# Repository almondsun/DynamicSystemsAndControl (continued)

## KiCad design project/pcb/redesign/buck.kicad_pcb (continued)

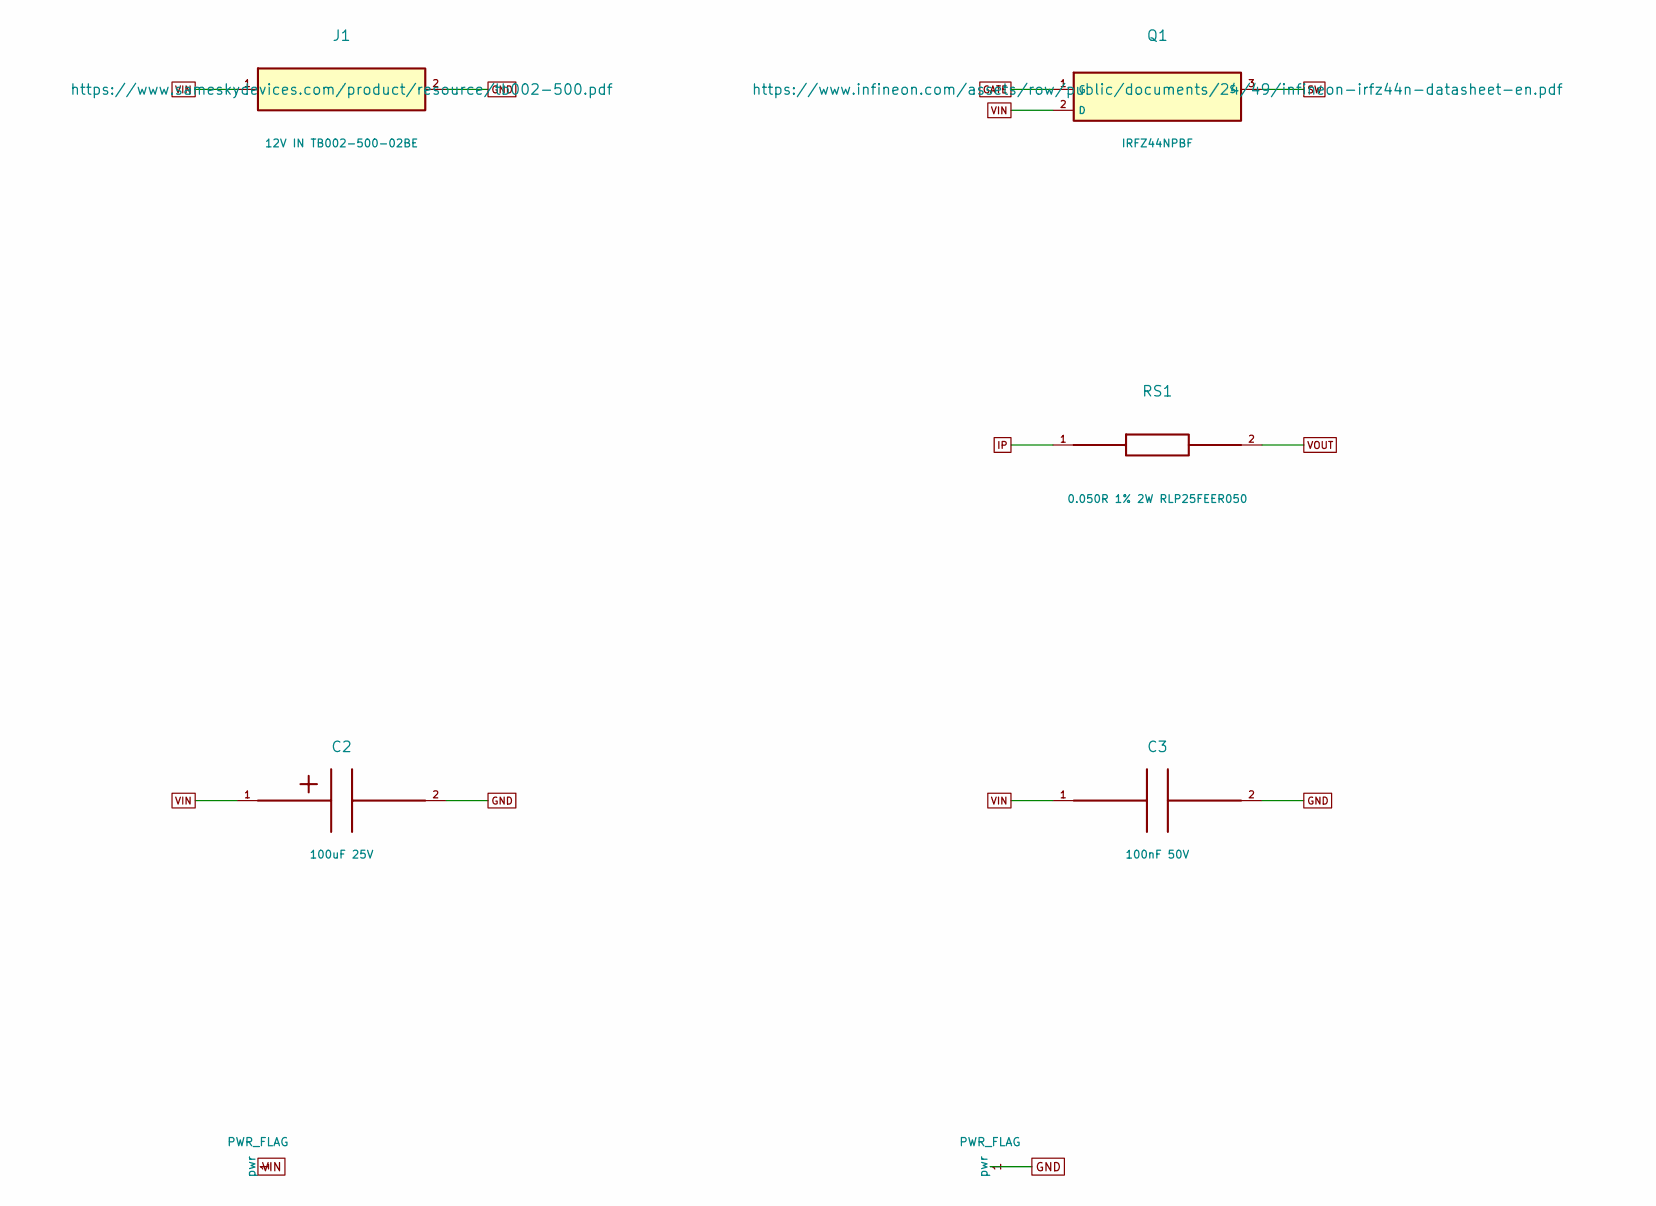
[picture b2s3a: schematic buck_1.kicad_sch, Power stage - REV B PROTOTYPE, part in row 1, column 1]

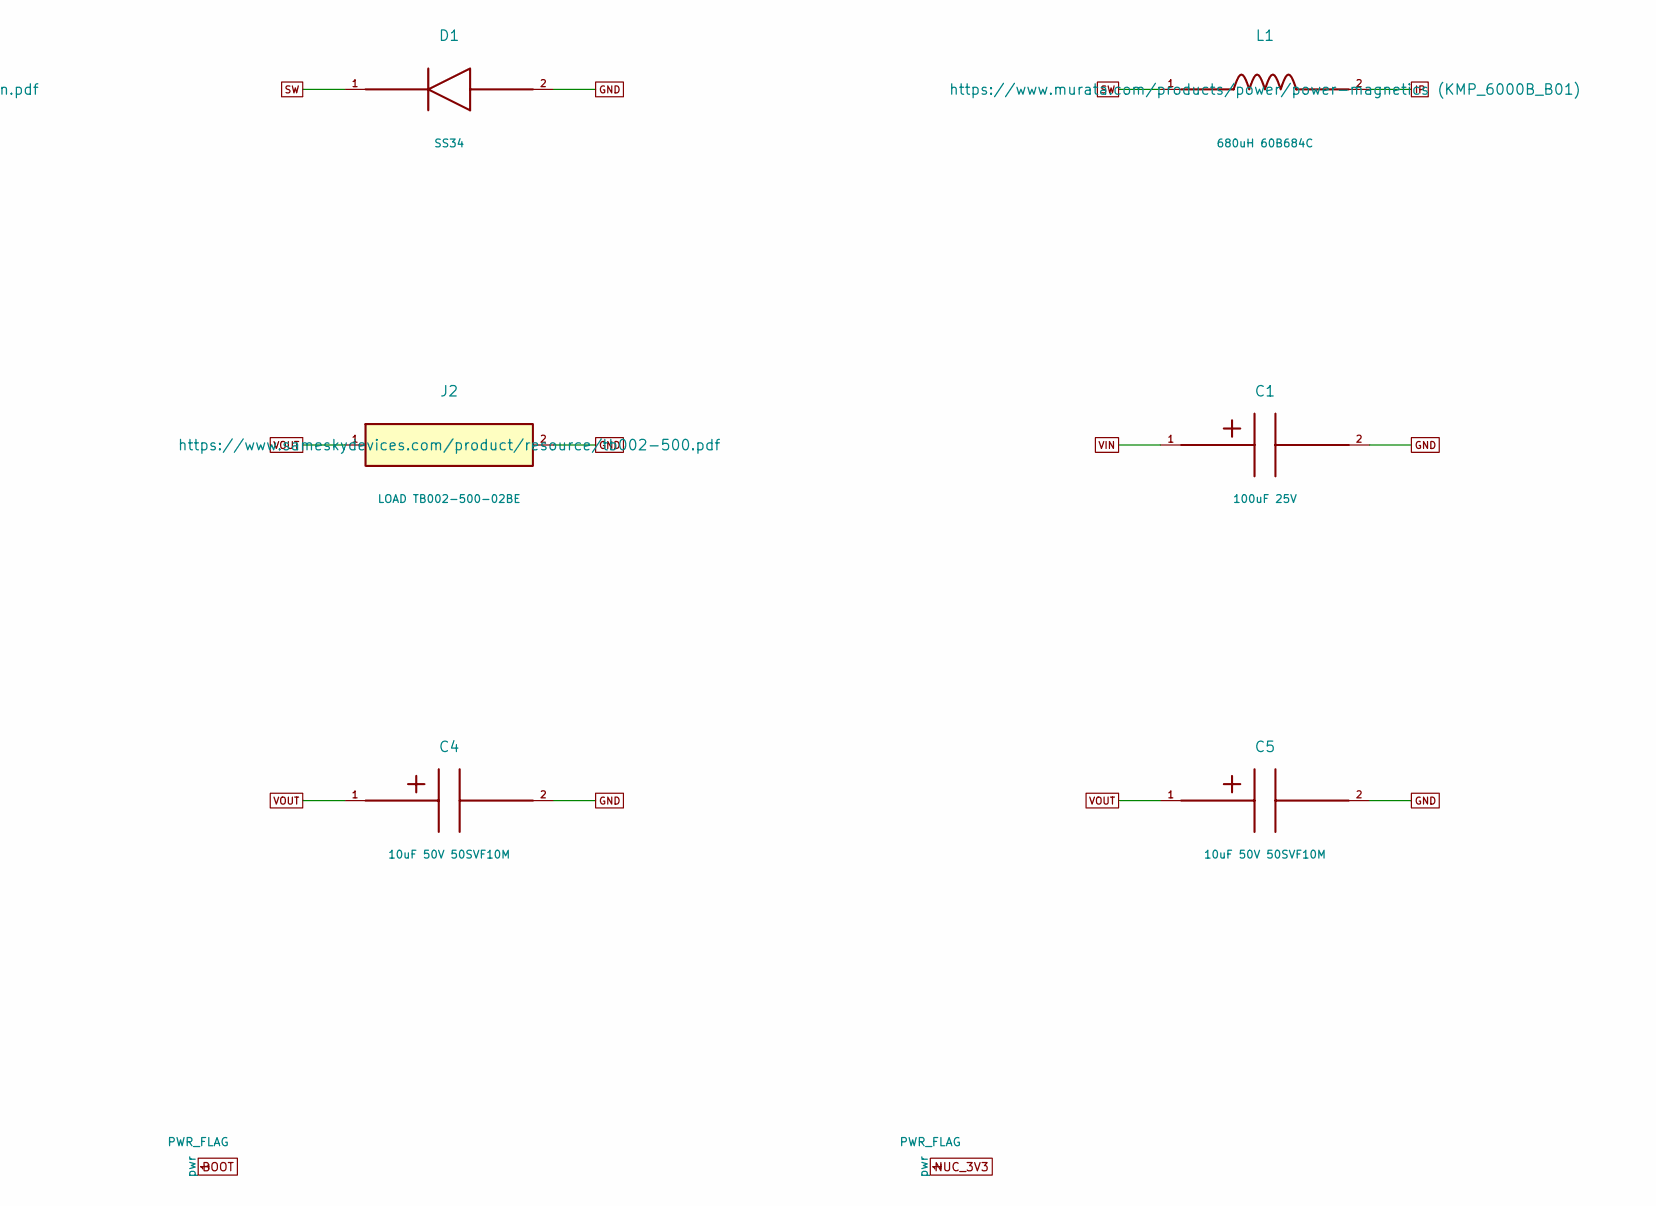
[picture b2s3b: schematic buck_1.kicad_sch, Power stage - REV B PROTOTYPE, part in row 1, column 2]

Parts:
C1, C2: 100uF 25V; CP_Panasonic_SVPF_E7_Land; MPN Panasonic 25SVPF100M; LCSC C136279
C3: 100nF 50V; C_0603_1608Metric; MPN Yageo CC0603KRX7R9BB104; LCSC C14663
C4, C5: 10uF 50V 50SVF10M; CP_Panasonic_SVF_C6_Land; MPN Panasonic 50SVF10M; LCSC C454354
D1: SS34; D_SMA; MPN SS34; LCSC C8678
J1: 12V IN TB002-500-02BE; TerminalBlock_SameSky_TB002-500-02_1x02_P5.00mm; MPN TB002-500-02BE; LCSC C2757858
J2: LOAD TB002-500-02BE; TerminalBlock_SameSky_TB002-500-02_1x02_P5.00mm; MPN TB002-500-02BE; LCSC C2757858
L1: 680uH 60B684C; L_Murata_6000B_27.0x23.5mm; MPN 60B684C; LCSC C6095796
Q1: IRFZ44NPBF; TO-220-3_Vertical_Drill1.4; MPN IRFZ44NPBF; LCSC C2586
RS1: 0.050R 1% 2W RLP25FEER050; R_TAI_RLP25_2512_Kelvin; MPN TA-I RLP25FEER050; LCSC C160588

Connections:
GATE: Q1.1 (G); also elsewhere on the board
GND: C1.2, C2.2, C3.2, C4.2, C5.2, D1.2, J1.2, J2.2; also elsewhere on the board
IP: L1.2, RS1.1; also elsewhere on the board
SW: D1.1, L1.1, Q1.3 (S); also elsewhere on the board
VIN: C1.1, C2.1, C3.1, J1.1, Q1.2 (D); also elsewhere on the board
VOUT: C4.1, C5.1, J2.1, RS1.2; also elsewhere on the board

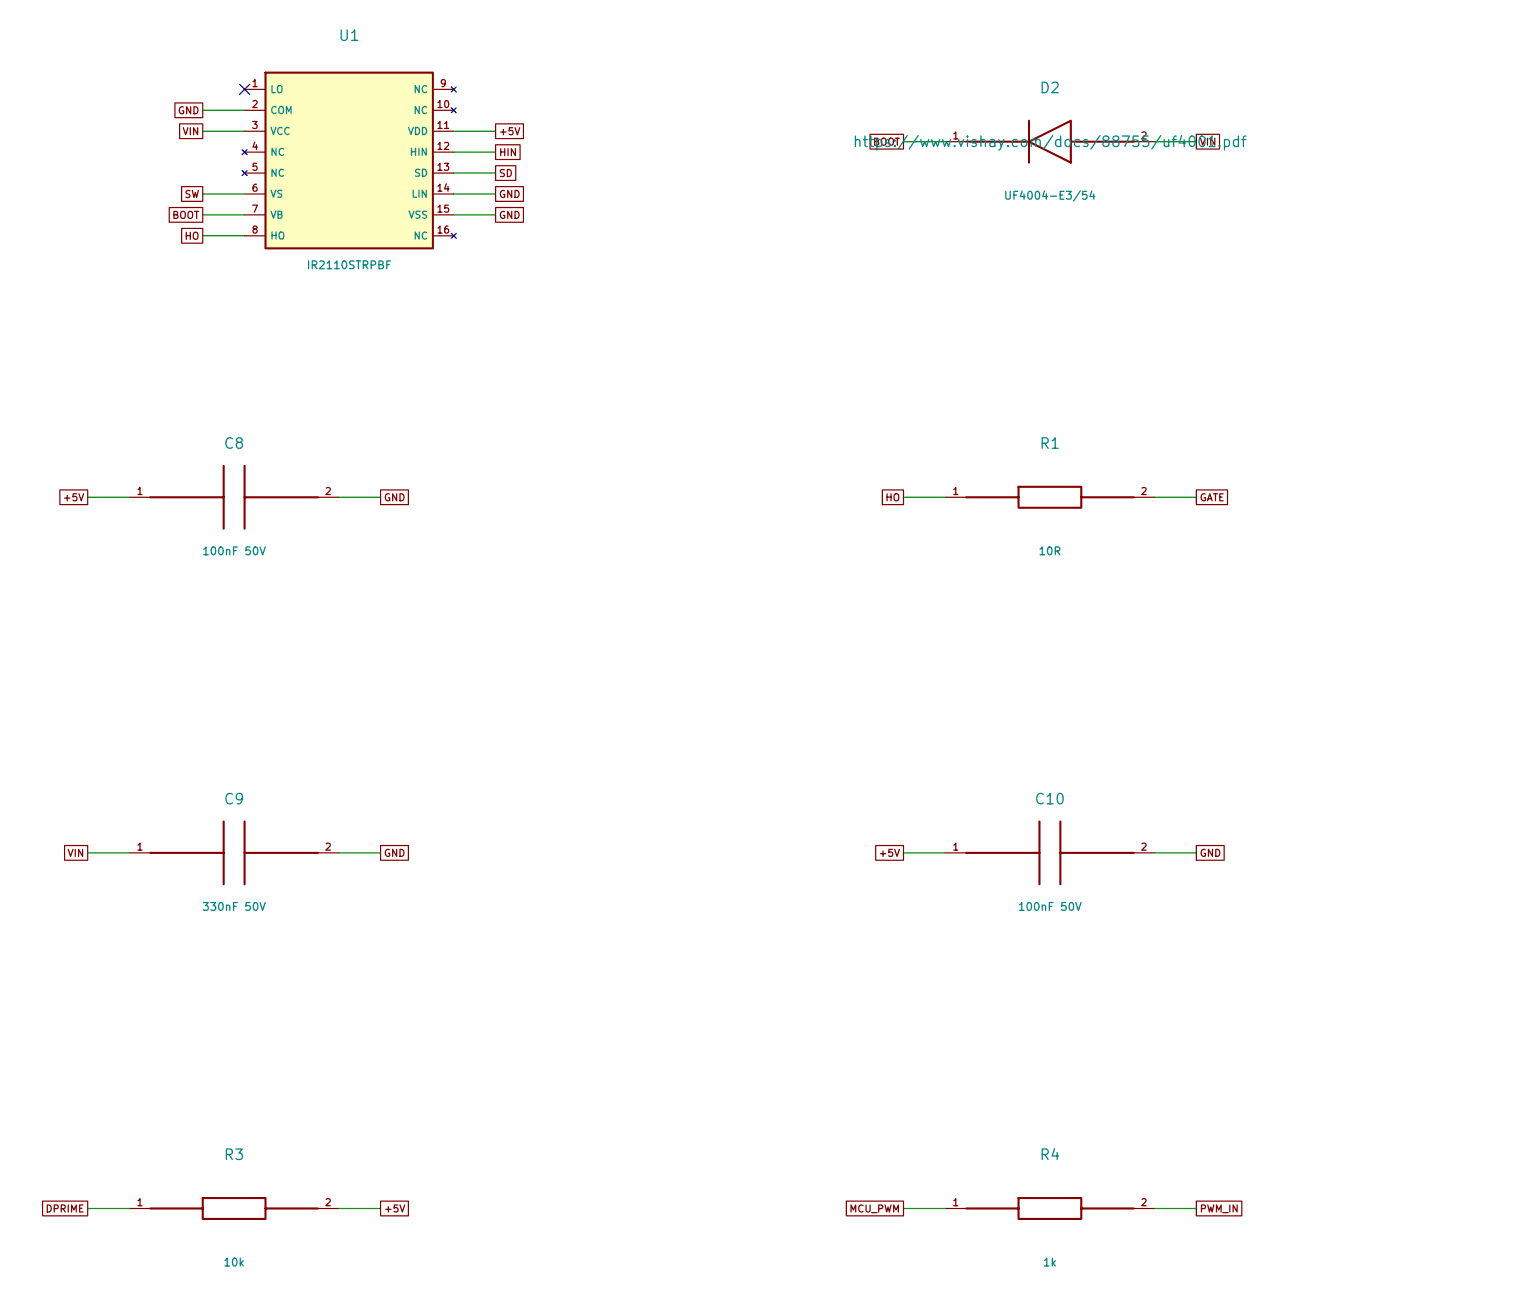
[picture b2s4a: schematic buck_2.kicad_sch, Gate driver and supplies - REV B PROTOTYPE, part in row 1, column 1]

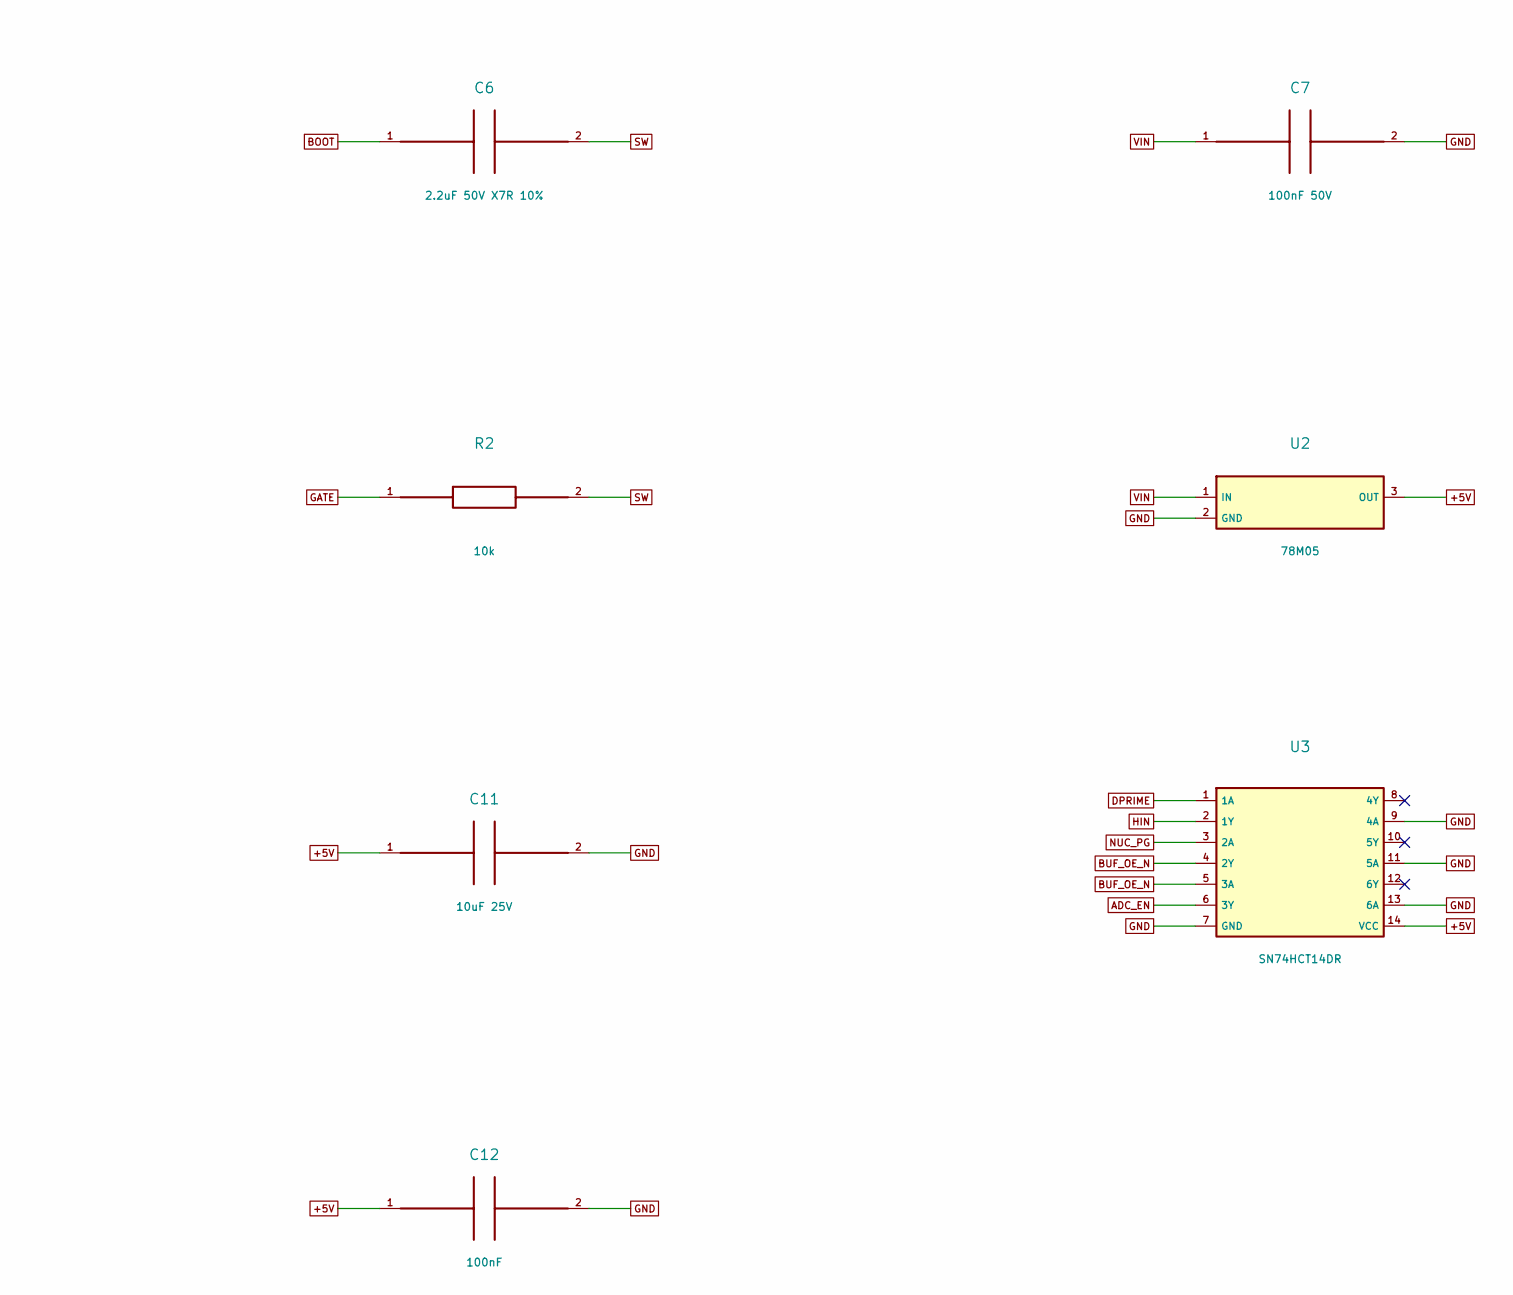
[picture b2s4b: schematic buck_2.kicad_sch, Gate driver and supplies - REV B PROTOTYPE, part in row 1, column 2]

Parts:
C6: 2.2uF 50V X7R 10%; C_1206_3216Metric; MPN CL31B225KBHNNNE; LCSC C50254
C7, C8, C10: 100nF 50V; C_0603_1608Metric; MPN Yageo CC0603KRX7R9BB104; LCSC C14663
C9: 330nF 50V; C_0805_2012Metric; MPN Samsung CL21B334KBFNNNE; LCSC C73142
C11: 10uF 25V; C_0805_2012Metric; MPN Samsung CL21A106KAYNNNE; LCSC C15850
C12: 100nF; C_0603_1608Metric; MPN Yageo CC0603KRX7R9BB104; LCSC C14663
D2: UF4004-E3/54; D_DO-41_SOD81_P10.16mm_Horizontal; MPN UF4004-E3/54; LCSC C5137033
R1: 10R; R_0805_2012Metric; MPN UNI-ROYAL 0805W8F100JT5E; LCSC C17415
R2, R3: 10k; R_0603_1608Metric; MPN UNI-ROYAL 0603WAF1002T5E; LCSC C25804
R4: 1k; R_0603_1608Metric; MPN UNI-ROYAL 0603WAF1001T5E; LCSC C21190
U1: IR2110STRPBF; SOIC-16W_7.5x10.3mm_P1.27mm; MPN IR2110STRPBF; LCSC C2968
U2: 78M05; TO-252-2; MPN 78M05; LCSC C347278
U3: SN74HCT14DR; TI_D0014A_SOIC-14; MPN SN74HCT14DR; LCSC C6769

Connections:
+5V: C8.1, C10.1, C11.1, C12.1, R3.2, U1.11 (VDD), U2.3 (OUT), U3.14 (VCC); also elsewhere on the board
ADC_EN: U3.6 (3Y); also elsewhere on the board
BOOT: C6.1, D2.1, U1.7 (VB)
BUF_OE_N: U3.4 (2Y), U3.5 (3A); also elsewhere on the board
DPRIME: R3.1, U3.1 (1A); also elsewhere on the board
GATE: R1.2, R2.1; also elsewhere on the board
GND: C7.2, C8.2, C9.2, C10.2, C11.2, C12.2, U1.2 (COM), U1.14 (LIN), U1.15 (VSS), U2.2 (GND), U3.7 (GND), U3.9 (4A), U3.11 (5A), U3.13 (6A); also elsewhere on the board
HIN: U1.12 (HIN), U3.2 (1Y)
HO: R1.1, U1.8 (HO)
MCU_PWM: R4.1; also elsewhere on the board
NUC_PG: U3.3 (2A); also elsewhere on the board
PWM_IN: R4.2; also elsewhere on the board
SD: U1.13 (SD); also elsewhere on the board
SW: C6.2, R2.2, U1.6 (VS); also elsewhere on the board
VIN: C7.1, C9.1, D2.2, U1.3 (VCC), U2.1 (IN); also elsewhere on the board

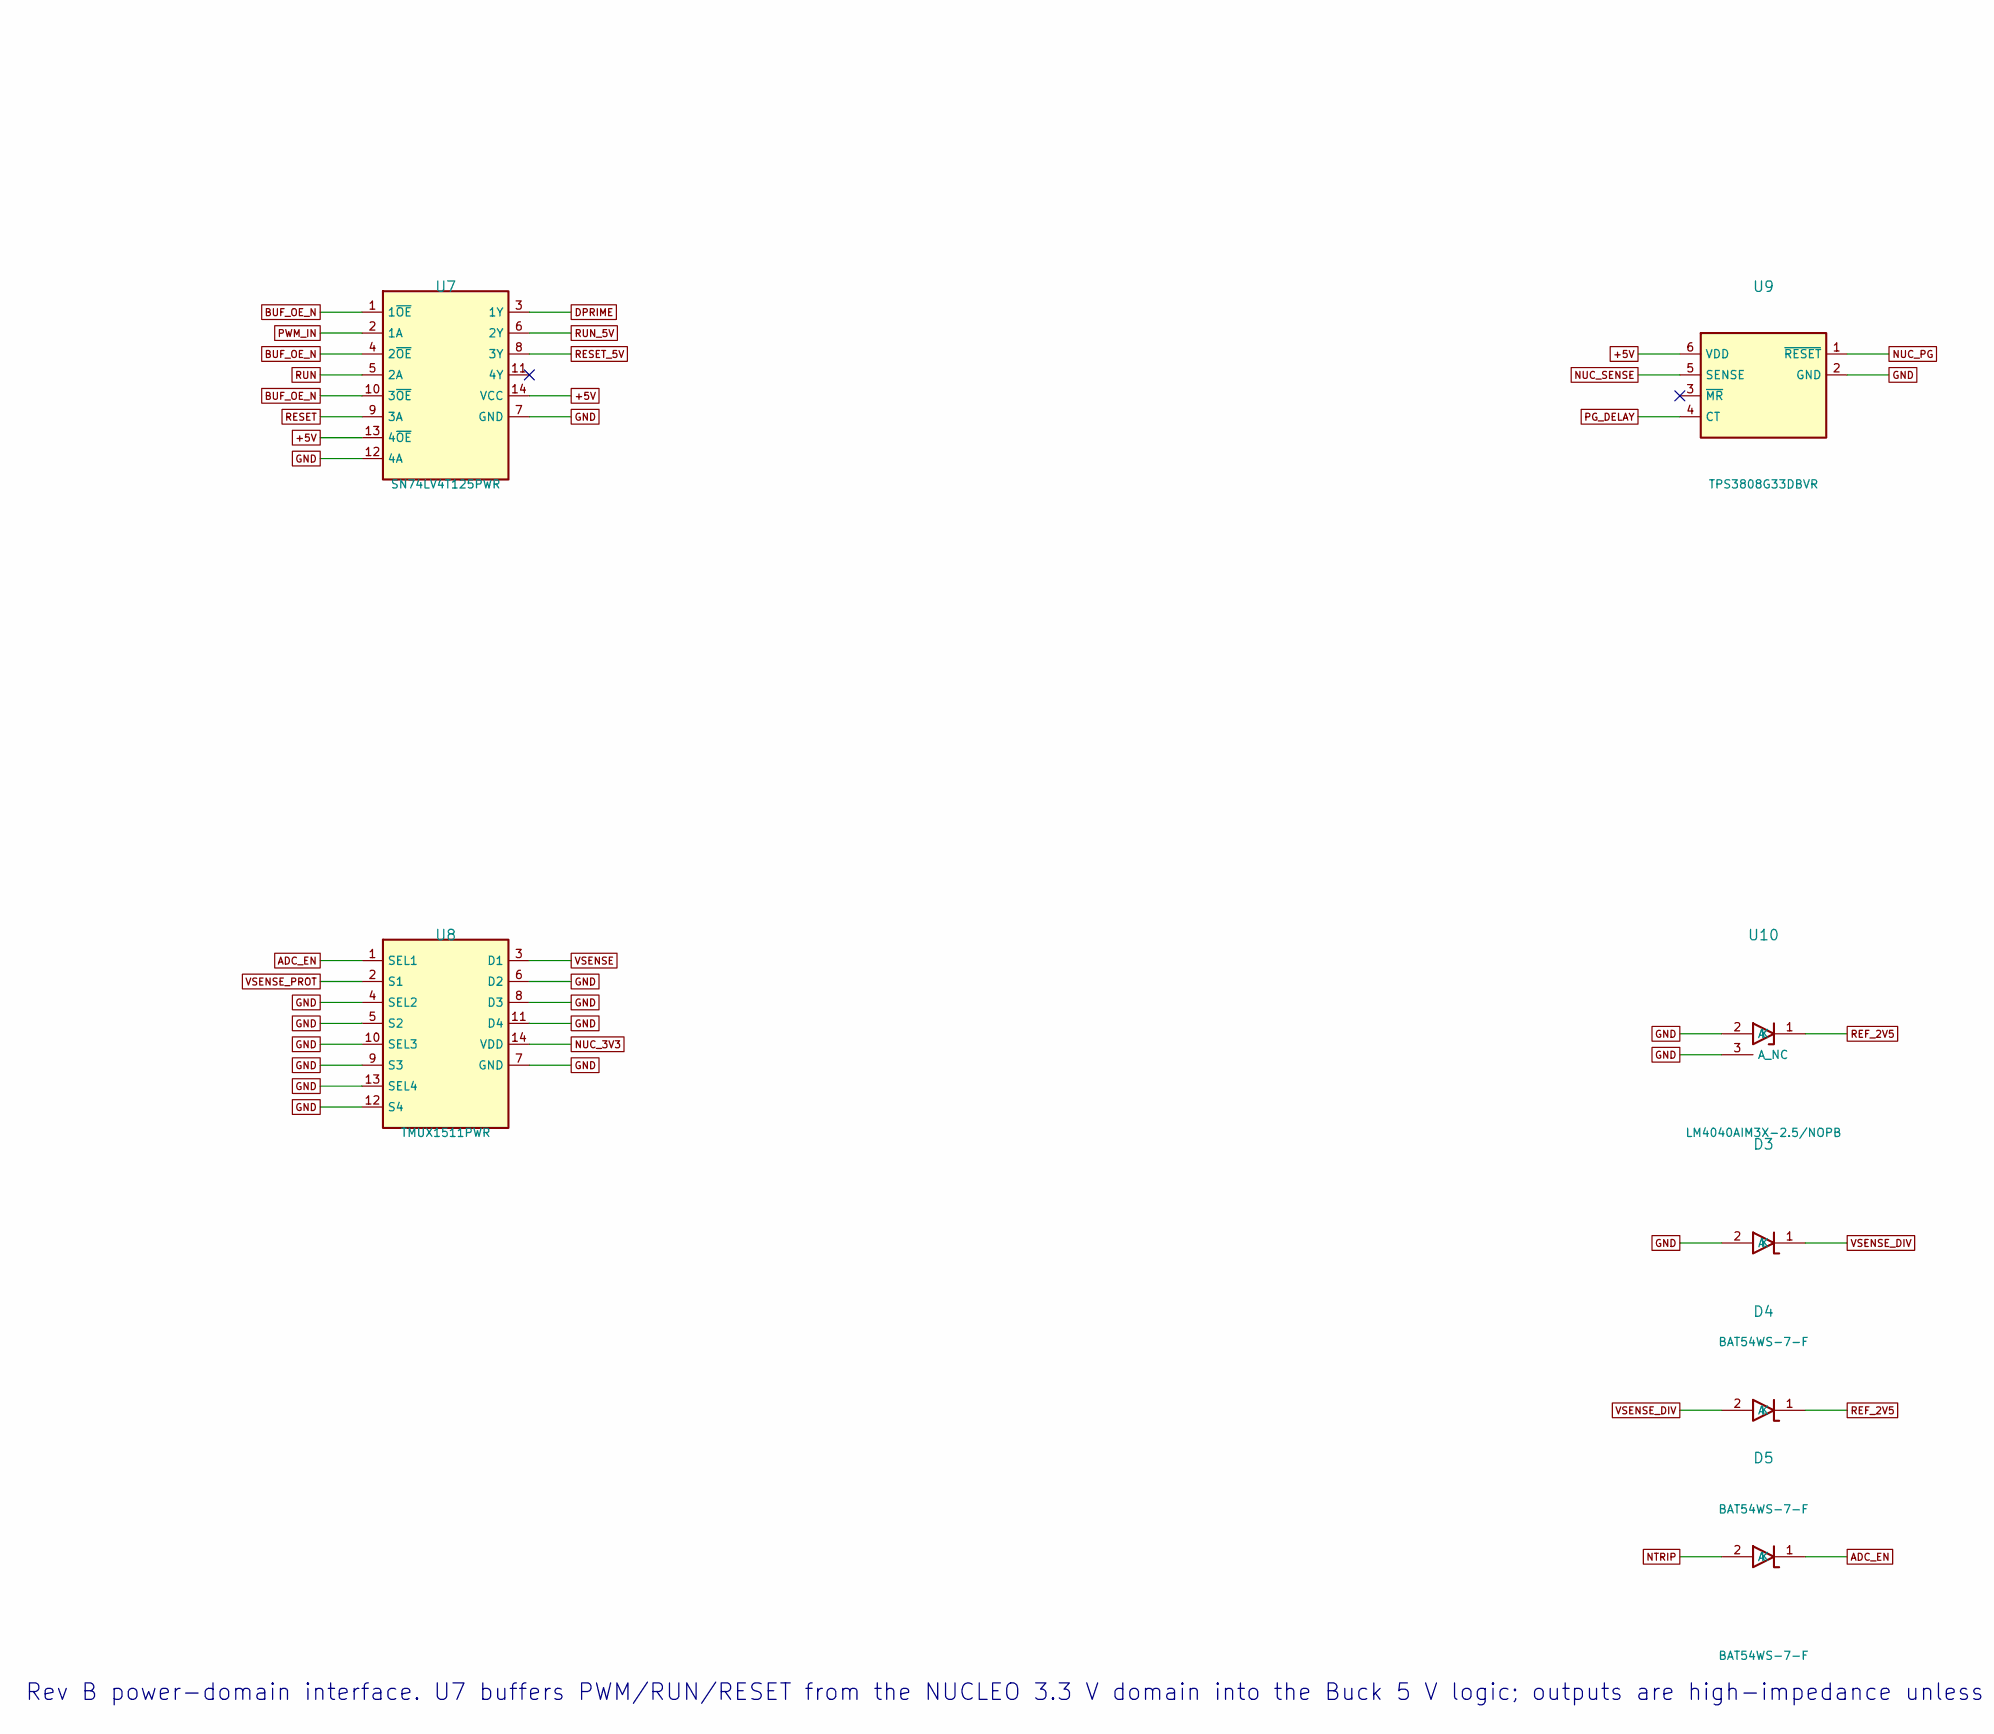
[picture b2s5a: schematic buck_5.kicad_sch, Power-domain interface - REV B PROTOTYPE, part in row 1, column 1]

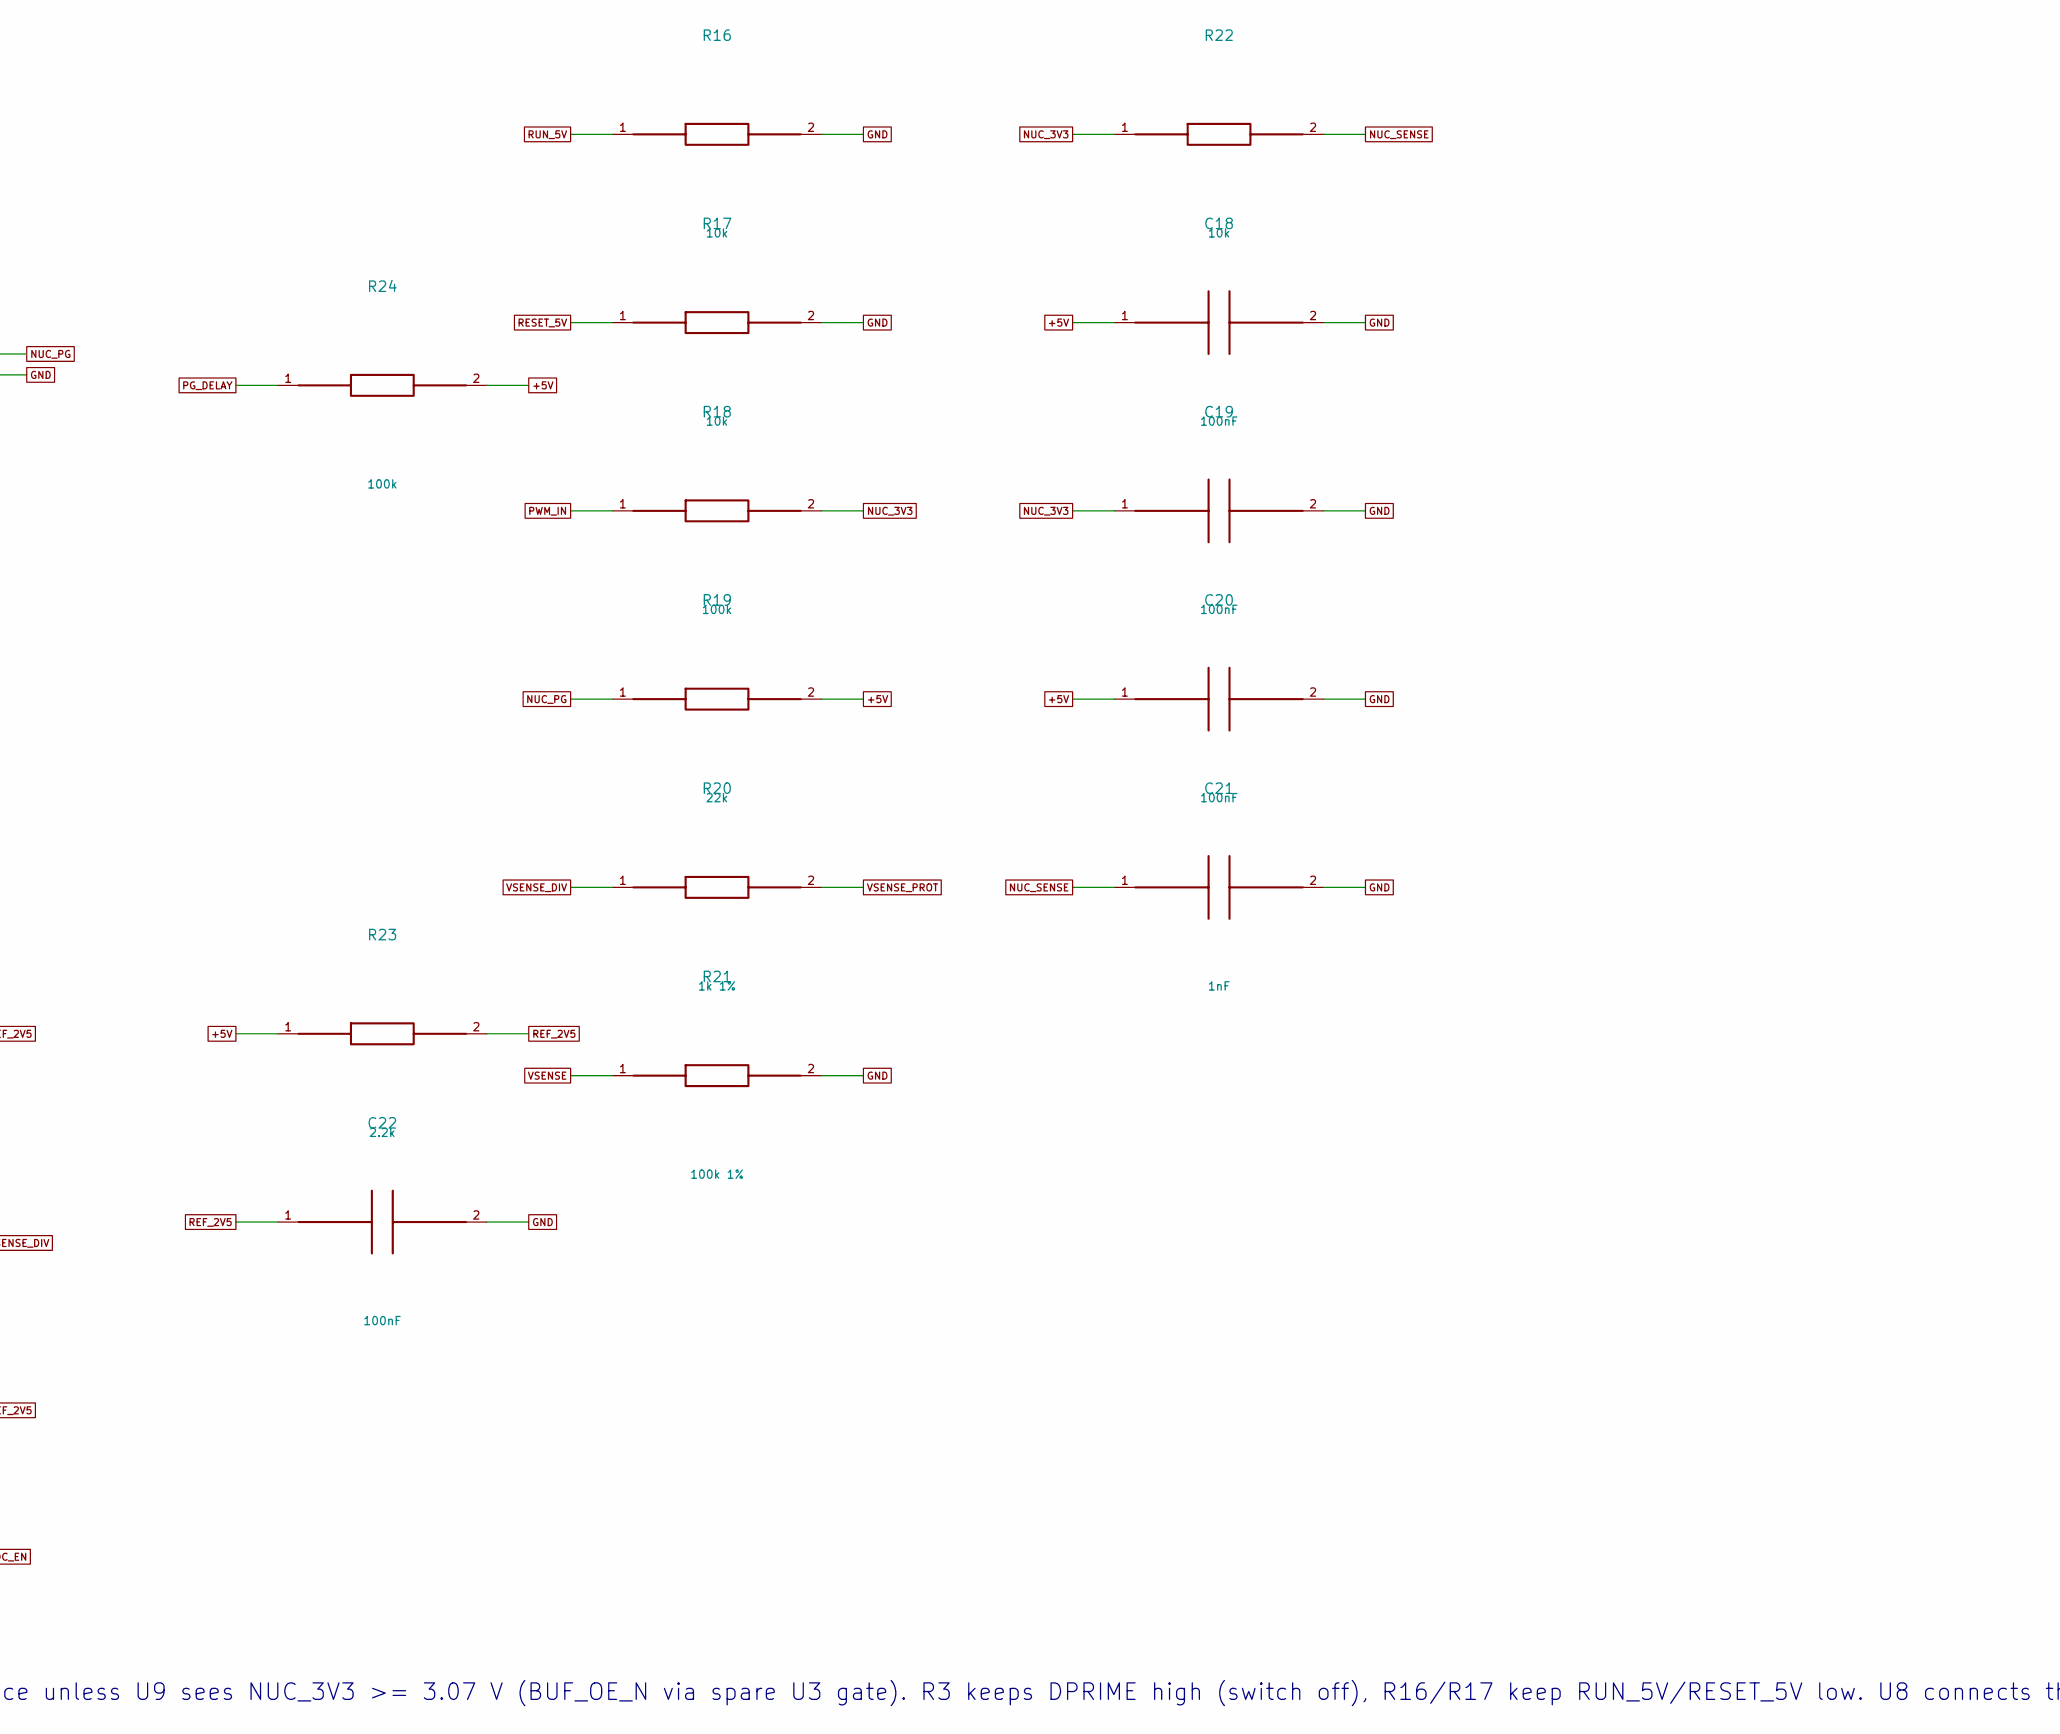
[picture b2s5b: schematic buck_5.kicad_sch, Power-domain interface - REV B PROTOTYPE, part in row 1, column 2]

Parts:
C18, C19, C20, C22: 100nF; C_0603_1608Metric; MPN CC0603KRX7R9BB104; LCSC C14663
C21: 1nF; C_0603_1608Metric; MPN 0603CG102J500NT; LCSC C1636
D3, D4, D5: BAT54WS-7-F; Diodes_SOD323; MPN BAT54WS-7-F; LCSC C124205
R16, R17, R22: 10k; R_0603_1608Metric; MPN 0603WAF1002T5E; LCSC C25804
R18, R24: 100k; R_0603_1608Metric; MPN 0603WAF1003T5E; LCSC C25803
R19: 22k; R_0603_1608Metric; MPN 0603WAF2202T5E; LCSC C31850
R20: 1k 1%; R_0603_1608Metric; MPN 0603WAF1001T5E; LCSC C21190
R21: 100k 1%; R_0603_1608Metric; MPN 0603WAF1003T5E; LCSC C25803
R23: 2.2k; R_0603_1608Metric; MPN 0603WAF2201T5E; LCSC C4190
U7: SN74LV4T125PWR; TI_PW0014A_TSSOP-14; MPN SN74LV4T125PWR; LCSC C90755
U8: TMUX1511PWR; TI_PW0014A_TSSOP-14; MPN TMUX1511PWR; LCSC C2866750
U9: TPS3808G33DBVR; TI_DBV0006A_SOT-23-6; MPN TPS3808G33DBVR; LCSC C43698
U10: LM4040AIM3X-2.5/NOPB; TI_DBZ0003A_SOT-23-3; MPN LM4040AIM3X-2.5/NOPB; LCSC C111866

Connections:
+5V: C18.1, C20.1, R19.2, R23.1, R24.2, U7.13 (4~OE), U7.14 (VCC), U9.6 (VDD); also elsewhere on the board
ADC_EN: D5.1 (K), U8.1 (SEL1); also elsewhere on the board
BUF_OE_N: U7.1 (1~OE), U7.4 (2~OE), U7.10 (3~OE); also elsewhere on the board
DPRIME: U7.3 (1Y); also elsewhere on the board
GND: C18.2, C19.2, C20.2, C21.2, C22.2, D3.2 (A), R16.2, R17.2, R21.2, U7.7 (GND), U7.12 (4A), U8.4 (SEL2), U8.5 (S2), U8.6 (D2), U8.7 (GND), U8.8 (D3), U8.9 (S3), U8.10 (SEL3), U8.11 (D4), U8.12 (S4), U8.13 (SEL4), U9.2 (GND), U10.2 (A), U10.3 (A_NC); also elsewhere on the board
NTRIP: D5.2 (A); also elsewhere on the board
NUC_3V3: C19.1, R18.2, R22.1, U8.14 (VDD); also elsewhere on the board
NUC_PG: R19.1, U9.1 (~RESET); also elsewhere on the board
NUC_SENSE: C21.1, R22.2, U9.5 (SENSE)
PG_DELAY: R24.1, U9.4 (CT)
PWM_IN: R18.1, U7.2 (1A); also elsewhere on the board
REF_2V5: C22.1, D4.1 (K), R23.2, U10.1 (K)
RESET: U7.9 (3A); also elsewhere on the board
RESET_5V: R17.1, U7.8 (3Y); also elsewhere on the board
RUN: U7.5 (2A); also elsewhere on the board
RUN_5V: R16.1, U7.6 (2Y); also elsewhere on the board
VSENSE: R21.1, U8.3 (D1); also elsewhere on the board
VSENSE_DIV: D3.1 (K), D4.2 (A), R20.1; also elsewhere on the board
VSENSE_PROT: R20.2, U8.2 (S1)

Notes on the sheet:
Rev B power-domain interface. U7 buffers PWM/RUN/RESET from the NUCLEO 3.3 V domain into the Buck 5 V logic; outputs are high-impedance unless U9 sees NUC_3V3 >= 3.07 V (BUF_OE_N via spare U3 gate). R3 keeps DPRIME high (switch off), R16/R17 keep RUN_5V/RESET_5V low. U8 connects the clamped ADC div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

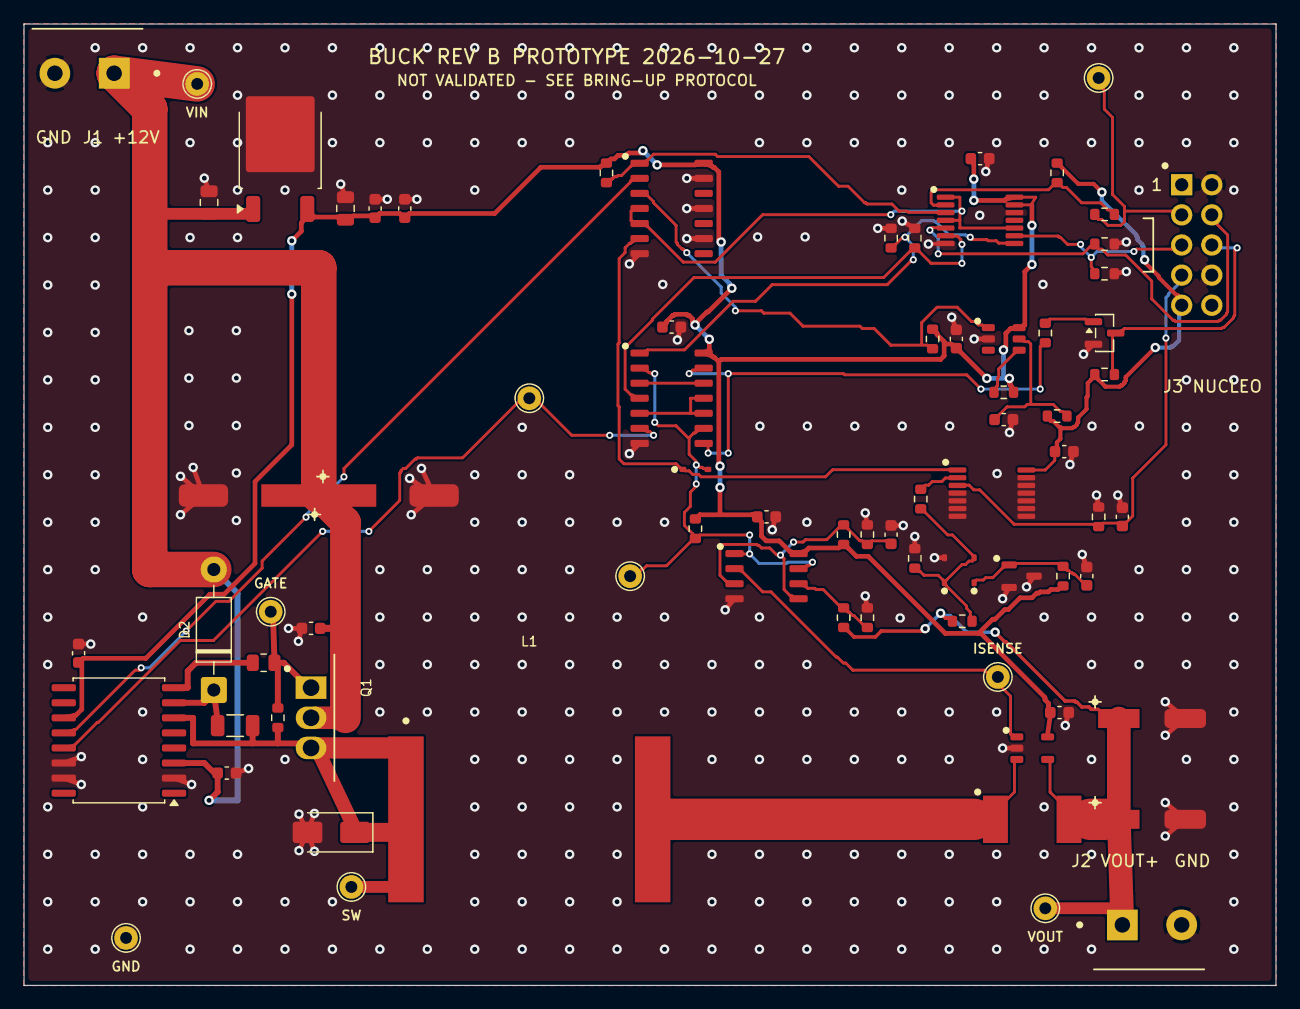
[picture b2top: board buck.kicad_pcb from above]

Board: 2 copper layers, 105.5 x 81.0 mm, 77 parts (0 on the bottom side), 37 nets.

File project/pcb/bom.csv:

Reference,Value,Footprint,Quantity,Qualification
J1,12V FUSED INPUT,"TerminalBlock_Phoenix:TerminalBlock_Phoenix_MKDS-1,5-2_1x02_P5.00mm_Horizontal",1,External 2A fast fuse; current-limited laboratory supply
Q1,IRFZ44N TO-220,Package_TO_SOT_THT:TO-220-3_Vertical,1,Gate/drain/source; metal tab VIN
D1,1N5822 40V 3A,Diode_THT:D_DO-201AD_P15.24mm_Horizontal,1,"Pin 1 cathode band, pin 2 anode"
L1,330uH >=3A Isat VERIFY,Buck:Inductor_25mm_P10mm_VERIFY,1,"Check actual dimensions, DCR and saturation before ordering PCB"
L2,330uH >=3A Isat VERIFY,Buck:Inductor_25mm_P10mm_VERIFY,1,"Check actual dimensions, DCR and saturation before ordering PCB"
RS1,0.050R 1% 1W,Resistor_SMD:R_2512_6332Metric,1,Kelvin sense at pads; CRCW2512 0R050 or verified equivalent
J2,LOAD + / -,"TerminalBlock_Phoenix:TerminalBlock_Phoenix_MKDS-1,5-2_1x02_P5.00mm_Horizontal",1,
C1,100uF 25V,Capacitor_THT:CP_Radial_D8.0mm_P3.50mm,1,Input bulk; positive pin 1
C2,100uF 25V,Capacitor_THT:CP_Radial_D8.0mm_P3.50mm,1,Input bulk; positive pin 1
C3,100nF 50V,Capacitor_THT:C_Disc_D5.0mm_W2.5mm_P5.00mm,1,
C4,10uF 35V low ESR,Capacitor_THT:CP_Radial_D6.3mm_P2.50mm,1,Exact 20uF total target; verify ripple rating and measured capacitance
C5,10uF 35V low ESR,Capacitor_THT:CP_Radial_D6.3mm_P2.50mm,1,Exact 20uF total target; verify ripple rating and measured capacitance
U1,IR2110PBF DIP14,Package_DIP:DIP-14_W7.62mm,1,
D2,UF4004,Diode_THT:D_DO-41_SOD81_P10.16mm_Horizontal,1,Bootstrap: cathode to BOOT
C6,1uF 50V X7R,Capacitor_THT:C_Disc_D5.0mm_W2.5mm_P5.00mm,1,
C7,100nF 50V,Capacitor_THT:C_Disc_D5.0mm_W2.5mm_P5.00mm,1,
C8,100nF 50V,Capacitor_THT:C_Disc_D5.0mm_W2.5mm_P5.00mm,1,
R1,10R,Resistor_THT:R_Axial_DIN0207_L6.3mm_D2.5mm_P7.62mm_Horizontal,1,
R2,10k,Resistor_THT:R_Axial_DIN0207_L6.3mm_D2.5mm_P7.62mm_Horizontal,1,
U2,L7805CV,Package_TO_SOT_THT:TO-220-3_Vertical,1,Input / ground / output; evaluate dissipation
C9,330nF 50V,Capacitor_THT:C_Disc_D5.0mm_W2.5mm_P5.00mm,1,
C10,100nF 50V,Capacitor_THT:C_Disc_D5.0mm_W2.5mm_P5.00mm,1,
C11,10uF 25V,Capacitor_THT:CP_Radial_D6.3mm_P2.50mm,1,
U3,SN74HCT14N,Package_DIP:DIP-14_W7.62mm,1,HCT TTL thresholds; do not substitute HC at 5V
R3,10k,Resistor_THT:R_Axial_DIN0207_L6.3mm_D2.5mm_P7.62mm_Horizontal,1,
R4,1k,Resistor_THT:R_Axial_DIN0207_L6.3mm_D2.5mm_P7.62mm_Horizontal,1,
C12,100nF,Capacitor_THT:C_Disc_D5.0mm_W2.5mm_P5.00mm,1,
U4,SN74HCT00N,Package_DIP:DIP-14_W7.62mm,1,Set-dominant NAND latch; SD = NOT(RUN AND NFAULT)
C13,100nF,Capacitor_THT:C_Disc_D5.0mm_W2.5mm_P5.00mm,1,
R5,10k,Resistor_THT:R_Axial_DIN0207_L6.3mm_D2.5mm_P7.62mm_Horizontal,1,
R6,10k,Resistor_THT:R_Axial_DIN0207_L6.3mm_D2.5mm_P7.62mm_Horizontal,1,
R7,4.7k,Resistor_THT:R_Axial_DIN0207_L6.3mm_D2.5mm_P7.62mm_Horizontal,1,
U5,LM393P,Package_DIP:DIP-8_W7.62mm,1,Two open-collector outputs wired together; overcurrent OR overvoltage
C14,100nF,Capacitor_THT:C_Disc_D5.0mm_W2.5mm_P5.00mm,1,
R8,15k 1%,Resistor_THT:R_Axial_DIN0207_L6.3mm_D2.5mm_P7.62mm_Horizontal,1,
R9,10k 1%,Resistor_THT:R_Axial_DIN0207_L6.3mm_D2.5mm_P7.62mm_Horizontal,1,
C15,100nF,Capacitor_THT:C_Disc_D5.0mm_W2.5mm_P5.00mm,1,
R10,31k 1%,Resistor_THT:R_Axial_DIN0207_L6.3mm_D2.5mm_P7.62mm_Horizontal,1,
R11,10k 1%,Resistor_THT:R_Axial_DIN0207_L6.3mm_D2.5mm_P7.62mm_Horizontal,1,
U6,INA180A1IDBVR,Package_TO_SOT_SMD:SOT-23-5,1,Pinout A ONLY; gain 20 V/V; sense RS1 pads directly
C16,100nF,Capacitor_THT:C_Disc_D5.0mm_W2.5mm_P5.00mm,1,
Q2,2N3904,Package_TO_SOT_THT:TO-92_Inline_Wide,1,E/B/C pin order must match purchased manufacturer
R12,10k,Resistor_THT:R_Axial_DIN0207_L6.3mm_D2.5mm_P7.62mm_Horizontal,1,
R13,10k,Resistor_THT:R_Axial_DIN0207_L6.3mm_D2.5mm_P7.62mm_Horizontal,1,
R14,3k 1%,Resistor_THT:R_Axial_DIN0207_L6.3mm_D2.5mm_P7.62mm_Horizontal,1,
R15,1k 1%,Resistor_THT:R_Axial_DIN0207_L6.3mm_D2.5mm_P7.62mm_Horizontal,1,
C17,1nF,Capacitor_THT:C_Disc_D5.0mm_W2.5mm_P5.00mm,1,
J3,STM32 CABLE 2x5,Connector_PinHeader_2.54mm:PinHeader_2x05_P2.54mm_Vertical,1,Key/polarize cable; external Blue Pill not integrated
TP1,VIN,TestPoint:TestPoint_THTPad_D2.0mm_Drill1.0mm,1,
TP2,GND,TestPoint:TestPoint_THTPad_D2.0mm_Drill1.0mm,1,
TP3,SW,TestPoint:TestPoint_THTPad_D2.0mm_Drill1.0mm,1,
TP4,GATE,TestPoint:TestPoint_THTPad_D2.0mm_Drill1.0mm,1,
TP5,VOUT,TestPoint:TestPoint_THTPad_D2.0mm_Drill1.0mm,1,
TP6,ISENSE,TestPoint:TestPoint_THTPad_D2.0mm_Drill1.0mm,1,
TP7,SD,TestPoint:TestPoint_THTPad_D2.0mm_Drill1.0mm,1,
TP8,NTRIP,TestPoint:TestPoint_THTPad_D2.0mm_Drill1.0mm,1,
TP9,MCU_PWM,TestPoint:TestPoint_THTPad_D2.0mm_Drill1.0mm,1,
